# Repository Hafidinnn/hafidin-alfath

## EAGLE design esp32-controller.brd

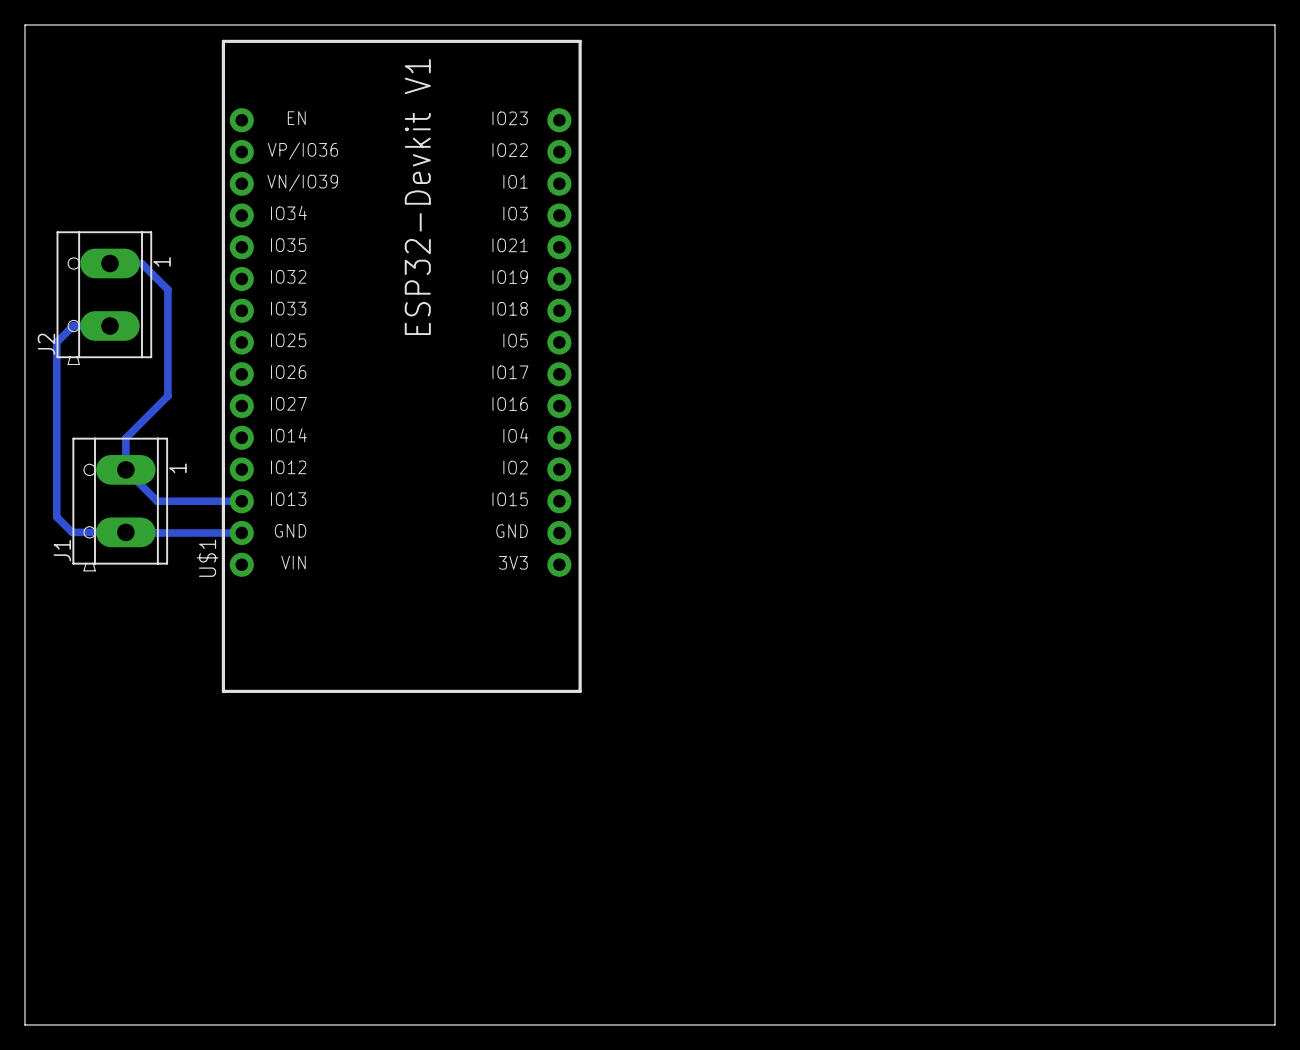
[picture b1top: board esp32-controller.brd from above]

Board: 2 copper layers, 100.0 x 80.0 mm, 3 parts (0 on the bottom side), 2 nets.

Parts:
J1, J2: CON_TERMINAL_BLOCK_02-5MM; TERMINAL_BLOCK_2P_5
U$1: ESP32DEVKITV1; ESP32-DEVKITV1

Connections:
GND: J1.1, J2.1, U$1.D13
HV: J1.2, J2.2, U$1.GND@1

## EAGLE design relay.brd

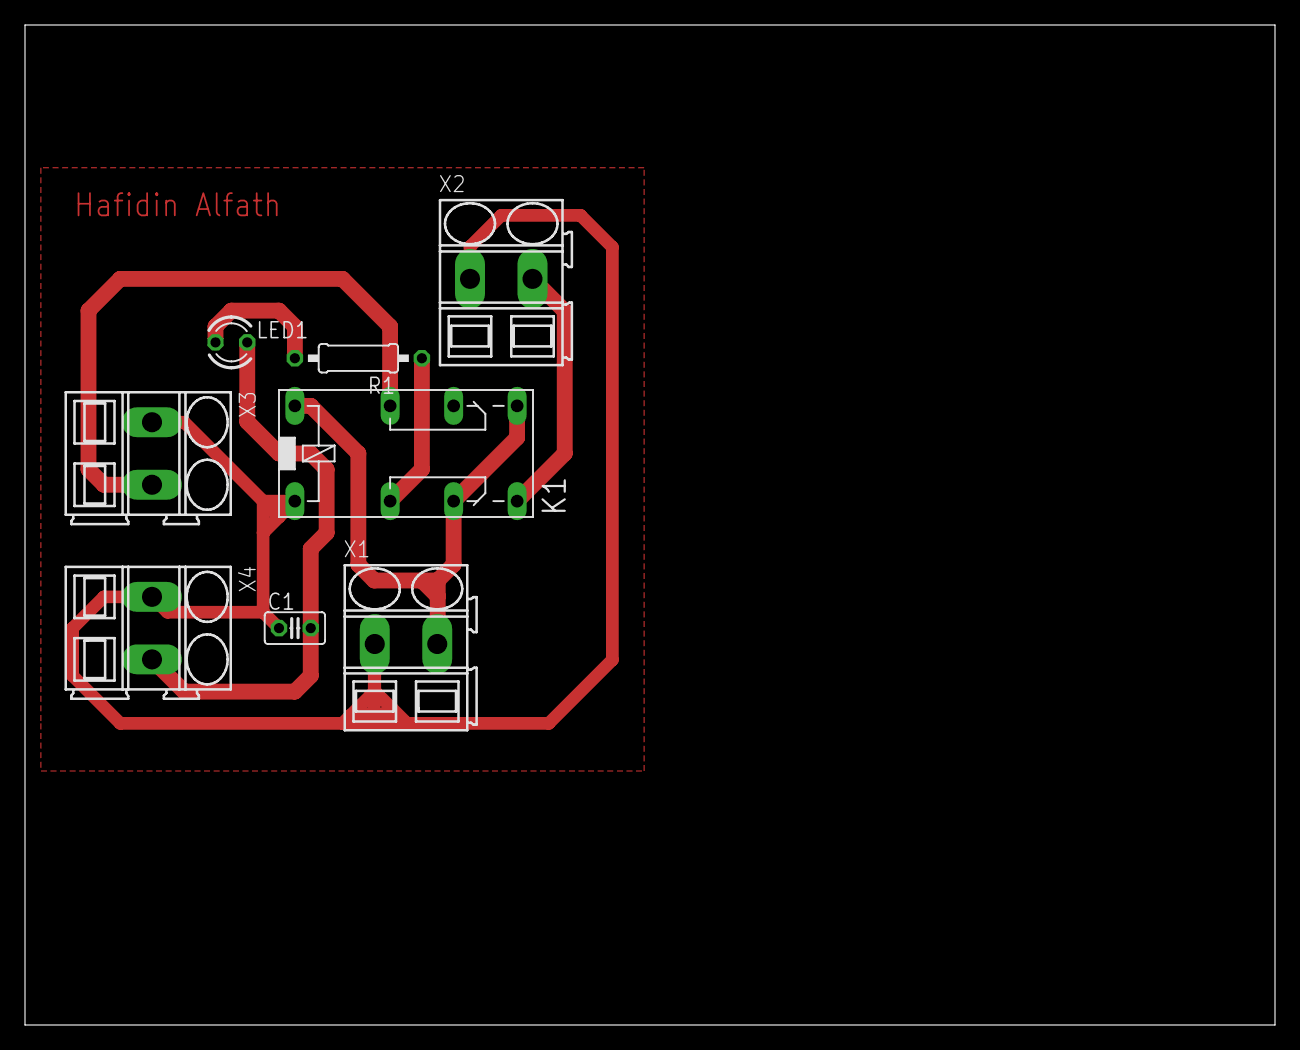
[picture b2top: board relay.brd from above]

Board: 2 copper layers, 100.0 x 80.0 mm, 8 parts (0 on the bottom side), 7 nets.

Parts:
C1: C025-025X050
K1: 351
LED1: LED3MM
R1: 0207/10
X1, X2, X3, X4: SMKDSP_1,5/2

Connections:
GND: C1.1, K1.1, X1.1, X2.1, X3.1, X4.1
unnamed: K1.P1, R1.1
unnamed: LED1.A, R1.2
O1: K1.S1, X2.2
P2: K1.P2, X3.2
S12: K1.16, K1.O1, K1.S2, X1.2
VOUT: C1.2, LED1.K, X4.2
